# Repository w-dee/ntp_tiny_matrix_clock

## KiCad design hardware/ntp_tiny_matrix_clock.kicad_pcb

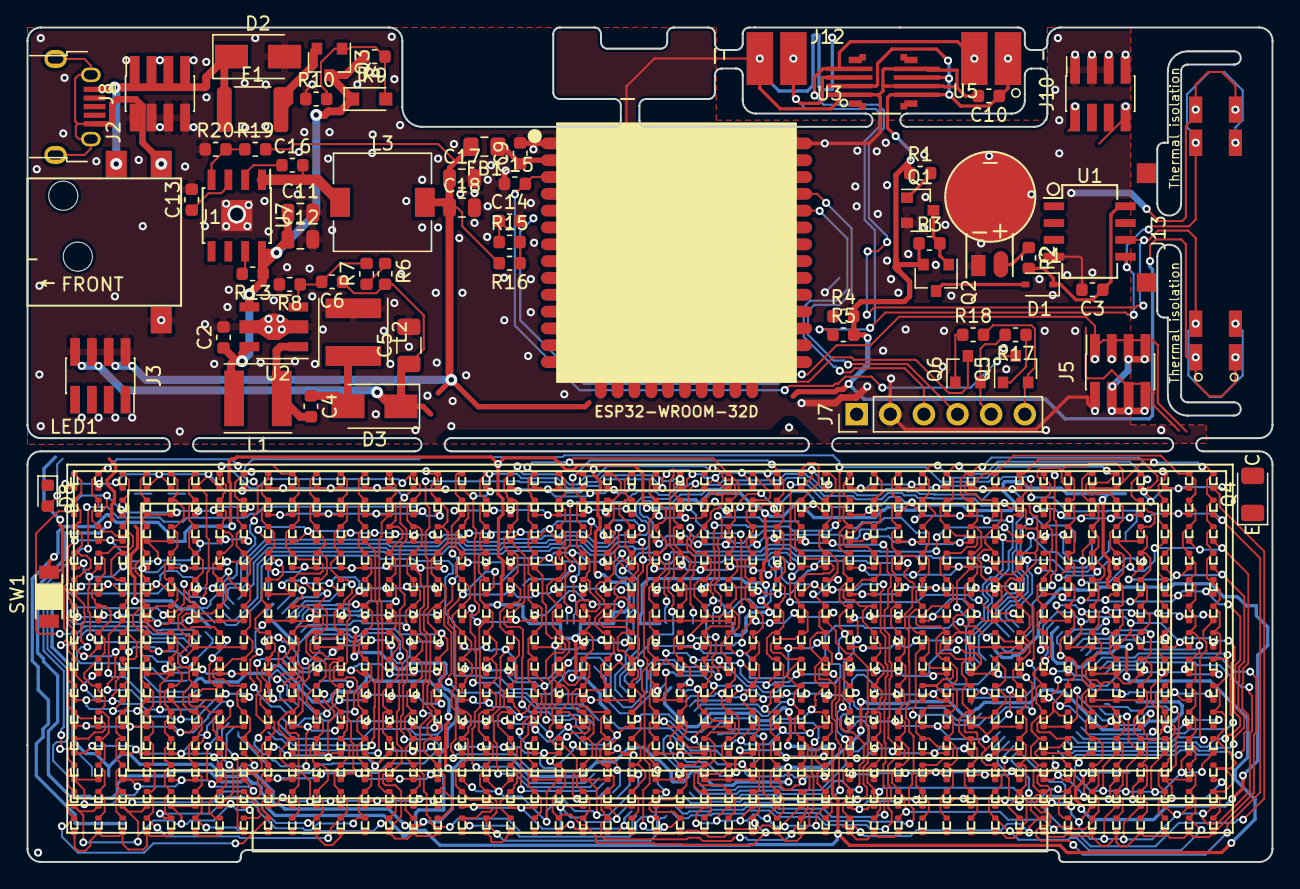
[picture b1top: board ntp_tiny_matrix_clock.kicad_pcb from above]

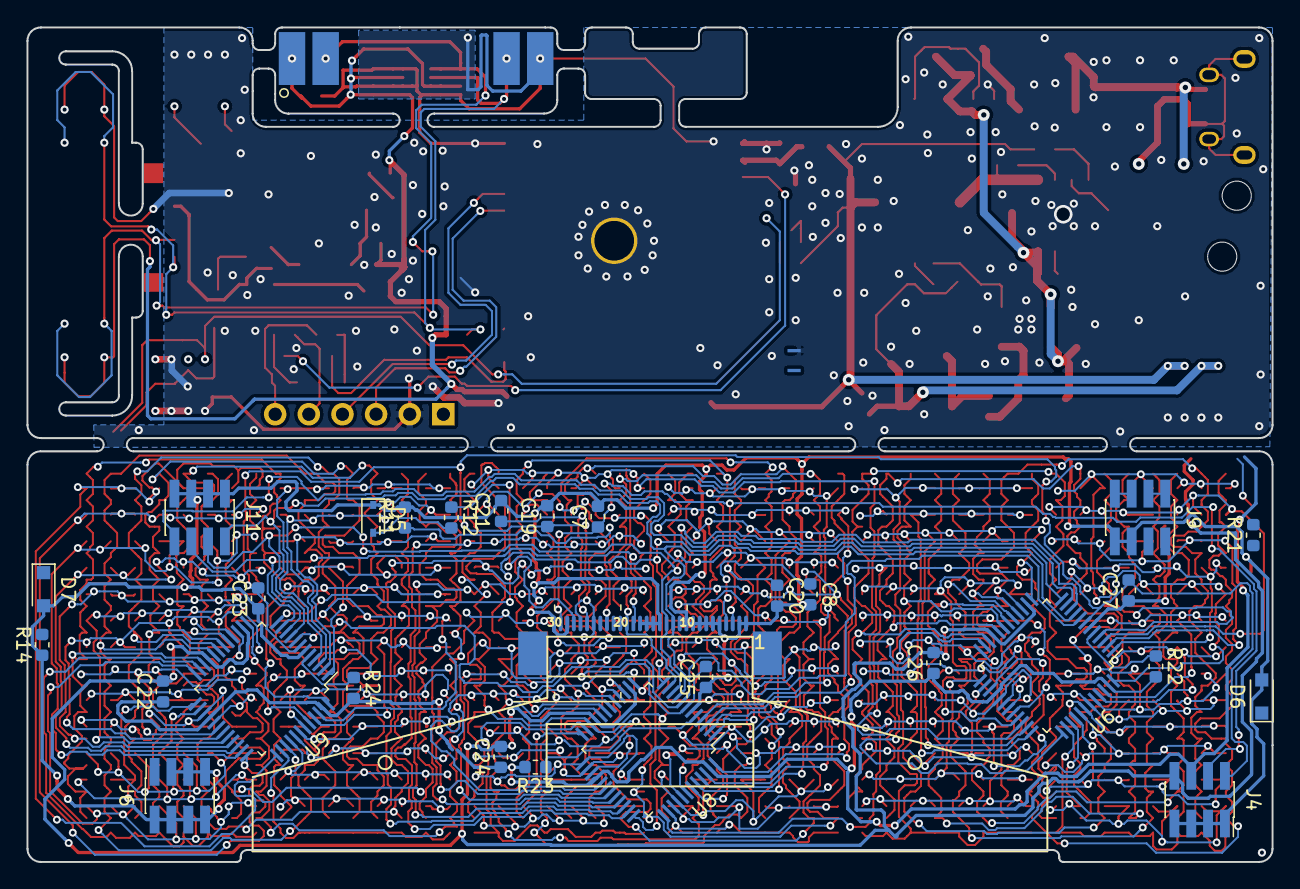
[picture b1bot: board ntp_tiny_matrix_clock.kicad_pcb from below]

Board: 2 copper layers, 94.0 x 63.0 mm, 96 parts (30 on the bottom side), 163 nets.

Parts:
C1: ML621; BAT_MS621T_LAY
C2, C4, C7, C19, C20, C21, C22, C23, C24, C25, C26, C27: 1u/50V; C_0603_1608Metric
C3, C15, C16: 0.1u; C_0603_1608Metric
C5: 10u/35V; C_1206_3216Metric
C6: 22p/50V; C_0603_1608Metric
C8: 4.7u/25V; C_0603_1608Metric
C9, C10: 1u; C_0603_1608Metric
C11, C12, C17, C18: 10u/35V; C_0805_2012Metric
C13, C14: 2.2u; C_0603_1608Metric
D1: SBD; D_SOD-323
D2: 28V TVS; D_SMA
D3: D_Schottky; D_SMA
D4, D6, D7: ESD5Z3.3T1G; D_SOD-323_HandSoldering
D5: Sillicon PN Junction; D_SOD-323
D8: LED_Small; LED_0603_1608Metric
F1: 1A hold; Fuse_1812_4532Metric
FB1: 300R@100MHz, 1A; L_0805_2012Metric_Pad1.15x1.40mm_HandSolder
J1: Barrel_Jack; DC-044-SMD
J2: USB_B_Micro; USB_Micro-B_Jing_A01SB141B1-067
J3, J4, J5, J6, J8, J9, J10, J11: Conn_02x04_Odd_Even; PinSocket_2x04_P1.27mm_Vertical_SMD
J7: Conn_01x06_Male; PinHeader_1x06_P2.54mm_Vertical
J12: Conn_01x04_Male; Board-Edge-4pin-DualSide-9.5mm-center-split
J13: Conn_01x04_Male; Board-Edge-4pin-DualSide-9.5mm-center-split-slit
JP1, JP2: Jumper_NC_Small; J_0.25mm
L1, L2: 22uH/200mA; L_Taiyo-Yuden_MD-5050
L3: 10uH; L_7.3x7.3_H3.5
LED1: LED48x14; led_matrix_0402_48x14
Q1, Q5, Q6: Q_NPN_BEC; SOT-23
Q2, Q3: AO3401; SOT-23
Q4: NJL7302L-F3; LED_1206_3216Metric
R1, R3, R7, R8, R14, R15, R17, R18: 10k; R_0603_1608Metric
R2, R22, R23, R24: 1k; R_0603_1608Metric
R4, R5, R21: 4.7k; R_0603_1608Metric
R6, R13: 100k; R_0603_1608Metric
R9: 1M; R_0603_1608Metric
R10: 22K; R_0603_1608Metric
R11: 620k; R_0603_1608Metric
R12: 50R; R_0603_1608Metric
R16: 22k; R_0603_1608Metric
R19: 49.9k; R_0603_1608Metric
R20: 16k; R_0603_1608Metric
SW1: SW_PUSH_SMALL_H; TACT_SW_SMD_Panasonic-EVPAWBD2A
U1: PCF8563; SOIC-8_3.9x7.0mm_Pitch1.27mm
U2: NJW4132U2-C; SOT-89-5
U3: ESP32-WROOM
U4: W256064-XALG; W256064-XALG-FOLD
U5: BME280; BME280-handsoldering-2
U6, U8, U9: HT16D35A; LQFP-48_7x7mm_P0.5mm
U7: JW5150A; SOIC-8-1EP_3.9x4.9mm_P1.27mm_EP2.35x2.35mm

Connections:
+3V3: C10.1, C17.1, C18.1, C19.1, C23.2, C25.2, C27.2, D8.2, FB1.2, J3.7, J4.2, J12.1, J13.1, JP1.1, L3.2, Q2.2, R1.1, R3.1, R4.2, R5.2, R16.2, R19.2, U4.24, U4.26, U5.2, U5.6, U5.8, U6.7, U8.7, U9.7
+12V: C5.1, C6.1, C7.1, C20.1, D3.1, J3.5, J4.4, R6.1, U4.3, U4.29
/3V3_RTC: C3.1, D1.1, R2.2, U1.8
/LD_OSC: U6.8, U8.8, U9.8
/LD_SYNC: U6.12, U8.12, U9.12
/LEDSPI_CS0: J10.8, J11.7, U6.11
/LED_VDD: C22.2, C24.2, C26.2, J3.1, J4.8, U6.14, U6.21, U8.14, U8.21, U9.14, U9.21
/LED_VSS: C22.1, C24.1, C26.1, J3.3, J4.6, R22.2, R23.2, R24.2, U6.28, U6.47, U8.28, U8.47, U9.28, U9.47
/VIN: C2.1, C11.1, C12.1, D4.1, L1.2, Q3.3, R9.2, R13.1, U2.4, U2.5, U7.8
/a0000: LED1.a0000, U6.13
/a0001: LED1.a0001, U6.15
/a0002: LED1.a0002, U6.16
/a0003: LED1.a0003, U6.17
/a0004: LED1.a0004, U6.18
/a0005: LED1.a0005, U6.19
/a0006: LED1.a0006, U6.20
/a0007: LED1.a0007, U6.22
/a0100: LED1.a0100, U8.13
/a0101: LED1.a0101, U8.15
/a0102: LED1.a0102, U8.16
/a0103: LED1.a0103, U8.17
/a0104: LED1.a0104, U8.18
/a0105: LED1.a0105, U8.19
/a0106: LED1.a0106, U8.20
/a0107: LED1.a0107, U8.22
/a0200: LED1.a0200, U9.13
/a0201: LED1.a0201, U9.15
/a0202: LED1.a0202, U9.16
/a0203: LED1.a0203, U9.17
/a0204: LED1.a0204, U9.18
/a0205: LED1.a0205, U9.19
/a0206: LED1.a0206, U9.20
/a0207: LED1.a0207, U9.22
/k0000: LED1.k0000, U6.4
/k0001: LED1.k0001, U6.3
/k0002: LED1.k0002, U6.2
/k0003: LED1.k0003, U6.1
/k0004: LED1.k0004, U6.48
/k0005: LED1.k0005, U6.46
/k0006: LED1.k0006, U6.45
/k0007: LED1.k0007, U6.44
/k0008: LED1.k0008, U6.43
/k0009: LED1.k0009, U6.42
/k0010: LED1.k0010, U6.41
/k0011: LED1.k0011, U6.40
/k0012: LED1.k0012, U6.39
/k0013: LED1.k0013, U6.38
/k0014: LED1.k0014, U6.37
/k0015: LED1.k0015, U6.36
/k0016: LED1.k0016, U6.35
/k0017: LED1.k0017, U6.34
/k0018: LED1.k0018, U6.33
/k0019: LED1.k0019, U6.32
/k0020: LED1.k0020, U6.31
/k0021: LED1.k0021, U6.30
/k0022: LED1.k0022, U6.29
/k0023: LED1.k0023, U6.27
/k0024: LED1.k0024, U6.26
/k0025: LED1.k0025, U6.25
/k0026: LED1.k0026, U6.24
/k0027: LED1.k0027, U6.23
/k0100: LED1.k0100, U8.4
/k0101: LED1.k0101, U8.3
/k0102: LED1.k0102, U8.2
/k0103: LED1.k0103, U8.1
/k0104: LED1.k0104, U8.48
/k0105: LED1.k0105, U8.46
/k0106: LED1.k0106, U8.45
/k0107: LED1.k0107, U8.44
/k0108: LED1.k0108, U8.43
/k0109: LED1.k0109, U8.42
/k0110: LED1.k0110, U8.41
/k0111: LED1.k0111, U8.40
/k0112: LED1.k0112, U8.39
/k0113: LED1.k0113, U8.38
/k0114: LED1.k0114, U8.37
/k0115: LED1.k0115, U8.36
/k0116: LED1.k0116, U8.35
/k0117: LED1.k0117, U8.34
/k0118: LED1.k0118, U8.33
/k0119: LED1.k0119, U8.32
/k0120: LED1.k0120, U8.31
/k0121: LED1.k0121, U8.30
/k0122: LED1.k0122, U8.29
/k0123: LED1.k0123, U8.27
/k0124: LED1.k0124, U8.26
/k0125: LED1.k0125, U8.25
/k0126: LED1.k0126, U8.24
/k0127: LED1.k0127, U8.23
/k0200: LED1.k0200, U9.4
/k0201: LED1.k0201, U9.3
/k0202: LED1.k0202, U9.2
/k0203: LED1.k0203, U9.1
/k0204: LED1.k0204, U9.48
/k0205: LED1.k0205, U9.46
/k0206: LED1.k0206, U9.45
/k0207: LED1.k0207, U9.44
/k0208: LED1.k0208, U9.43
/k0209: LED1.k0209, U9.42
/k0210: LED1.k0210, U9.41
/k0211: LED1.k0211, U9.40
/k0212: LED1.k0212, U9.39
/k0213: LED1.k0213, U9.38
/k0214: LED1.k0214, U9.37
/k0215: LED1.k0215, U9.36
/k0216: LED1.k0216, U9.35
/k0217: LED1.k0217, U9.34
/k0218: LED1.k0218, U9.33
/k0219: LED1.k0219, U9.32
/k0220: LED1.k0220, U9.31
/k0221: LED1.k0221, U9.30
/k0222: LED1.k0222, U9.29
/k0223: LED1.k0223, U9.27
/k0224: LED1.k0224, U9.26
/k0225: LED1.k0225, U9.25
/k0226: LED1.k0226, U9.24
/k0227: LED1.k0227, U9.23
DTR: J7.5, Q6.2, R17.2
E_AIN: C14.1, D7.1, J5.7, J6.1, Q4.2, R14.2, R15.1, U3.5
E_BUTTON: D6.1, J8.2, J9.1, SW1.2, U3.7
E_EN: C15.2, Q5.3, U3.3
E_GPIO0: Q6.3, U3.25
E_RX: J7.3, U3.34
E_TX: J7.4, U3.35
GND: C1.2, C2.2, C3.2, C5.2, C7.2, C8.2, C9.2, C10.2, C11.2, C12.2, C13.2, C14.2, C15.1, C17.2, C18.2, C19.2, C20.2, C21.2, C23.1, C25.1, C27.1, D2.2, D5.1, D6.2, D7.2, J1.2, J3.2, J3.4, J3.6, J3.8, J4.1, J4.3, J4.5, J4.7, J5.1, J5.2, J5.3, J5.4, J5.5, J5.6, J5.8, J6.2, J6.3, J6.4, J6.5, J6.6, J6.7, J6.8, J7.2, J8.1, J8.3, J8.5, J8.6, J8.7, J8.8, J9.2, J9.4, J9.5, J9.6, J9.7, J9.8, J10.3, J10.5, J10.7, J11.4, J11.6, J11.8, J12.4, J13.4, JP2.1, L2.1, Q1.2, Q4.1, R8.2, R10.1, R11.2, R14.1, R20.1, SW1.1, U1.4, U2.2, U3.1, U3.15, U3.38, U3.39, U4.1, U4.2, U4.5, U4.6, U4.7, U4.8, U4.9, U4.10, U4.14, U4.15, U4.16, U4.17, U4.28, U4.30, U5.1, U5.5, U5.7, U6.6, U7.9, U8.6, U9.6
LED_RLAT: J10.6, J11.5, U3.8, U4.18, U9.11
LED_SCK: J10.4, J11.3, U3.31, U4.13, U6.10, U8.10, U9.10
LED_SOUT: J10.2, J11.1, U3.30, U4.12, U6.9, U8.9, U9.9
LED_~SLAT: J10.1, J11.2, U3.29, U4.19, U8.11
unnamed: C1.1, R2.1
unnamed: C4.1, D3.2, L2.2
unnamed: C4.2, L1.1, U2.1
unnamed: C6.2, R7.2, R8.1, U2.3
unnamed: C8.1, U4.4
unnamed: C9.1, FB1.1, U3.2
unnamed: C13.1, U7.3
unnamed: C16.1, U7.2
unnamed: C16.2, L3.1, U7.1
unnamed: C21.1, U4.25
unnamed: D1.2, Q2.3
unnamed: D2.1, F1.1, J1.1, J2.1
unnamed: D4.2, Q3.1, R9.1, R10.2
unnamed: D5.2, R12.2
unnamed: D8.1, R21.2
unnamed: F1.2, Q3.2
unnamed: J1.3, J2.5, J2.6
unnamed: Q1.1, R1.2
unnamed: Q1.3, Q2.1, R3.2
unnamed: Q5.1, R17.1
unnamed: Q6.1, R18.1
unnamed: R6.2, R7.1
unnamed: R11.1, U4.22
unnamed: R12.1, U4.27
unnamed: R13.2, U7.7
unnamed: R15.2, R16.1
unnamed: R19.1, R20.2, U7.4
unnamed: R22.1, U6.5
unnamed: R23.1, U8.5
unnamed: R24.1, U9.5
RTS: J7.6, Q5.2, R18.2
SCL: J12.2, J13.2, R4.1, U1.6, U5.4
SDA: J12.3, J13.3, R5.1, U1.5, U3.27, U5.3
STATUS: J8.4, J9.3, R21.1, U3.26

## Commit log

2018-11-22 Layout and traces fix
2018-12-01 to use holtek led driver
2018-12-10 LED matrix circuit trace design ongoing. Too much difficult.
2018-12-11 Almost all connection done; Traces are too narrow to keep signal integrity but there is no space left. sigh
2018-12-12 Routing ongoing...
